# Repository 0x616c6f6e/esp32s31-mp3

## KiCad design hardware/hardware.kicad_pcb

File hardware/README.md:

# ESP32-S31 MP3 · 紧凑版硬件 Rev A

本目录为基于原始嘉立创工程迁移、修正并缩小的 KiCad 10 工程。PCB 为 **48 × 76 mm、六层、R1.2 mm 圆角**，比原版 50 × 80 mm 面积减少 **8.8%**。这是可继续编辑和结构评审的版本，尚未完成整机装配及实物电气验证。

## 打开与预览

使用 **KiCad 10.0.4 或兼容版本**打开 `hardware.kicad_pro`，从项目管理器进入原理图和 PCB。符号、封装均使用本目录相对路径，不依赖嘉立创在线库。

- `hardware.kicad_sch`：总览及九张子页。
- `hardware.kicad_pcb`：126 个封装，已布线、铺铜。
- `MP3_Source.kicad_sym`、`MP3_Source.pretty/`：工程内符号和 42 个封装文件。
- `output/layout-overview.png`：正反面布局和尺寸预览。
- `output/assembly-top.svg`、`assembly-bottom.svg`：实际封装装配图。
- `output/schematic/`：十张原理图 SVG。
- `output/board-only.step`：KiCad 导出的板体 STEP；FreeCAD 实体复核为 48 × 76 × 0.91 mm，导出板体未包含外表铜及阻焊的厚度。结构预留应按暂定名义板厚 1.0 mm 加公差计算；不含元件、屏幕、电池或外壳。
- `output/pcb-top.png`：KiCad 裸板渲染。原始工程没有可用的完整元件三维模型，不能用它判断器件高度。
- `output/drc.json`、`erc.json`、`netlist.xml`、`validation-summary.json`：检查报告及网络表。

## 本次修改

1. 从 `.epro2` 原工程导出兼容的 EasyEDA Pro V2 工程，再用 KiCad 原生导入，保留原器件封装和六层连接。原始 Gerber 作为原版层数和外形依据；新板没有直接复用 Gerber 图形充当可编辑布线。
2. 保留顶部 TF 卡座、右上主控、左下音频、右下充电供电、底部 USB-C / 耳机座、背面屏幕 FPC 的功能布局；压缩功能区间隙并收紧外框，重布受影响网络和局部地连接。
3. 修复跨页网络标签、短接符号和导入形成的微小断线；统一网络别名，记录在 `reference/net-aliases.json`。原理图网格整理和悬空线段清理前后，168 组“器件引脚集合”的连接分组保持一致。
4. 按 CS43131 数据手册修正 U2 的 I²C 引脚：**1 脚 SCL、39 脚 SDA**，并同步修正 PCB。补全 C32 / C33 晶振电容的原理图接地。修正可选下载电路的 BOOT 网络名。
5. 校正主要芯片引脚电气类型和电源驱动标识；保留原工程排除出 PCB 的可选电路，不将缺件强行补装。排除项包括 Q1、Q2、R23、R24、C13、R15、R16、U10、R6、C52、C60；具体以原理图的 `on_board` / DNP 属性为准。
6. 将原来落在 Edge.Cuts 上、不能约束铜层的天线禁布区修正为六层铜禁布，重新铺铜。板顶约 6.169 mm 范围禁止走线、过孔、铺铜；为保留 SCREW5 非金属化孔，区域允许焊盘对象，另外核对现有铜焊盘均未侵入此区域。以后移动或增加器件时必须重新核对。
7. 移除原版板框外的 SCREW3，将其余四个安装孔改为 Ø2.2 mm NPTH，供 M2 安装使用。源封装中的零环宽镀铜孔不再沿用。
8. 将不适合印刷的源封装轮廓转到 Fab 层，整理原理图页框、说明和目录，清除无效导入图形。装配时应参考 Fab 图；生产丝印仍应按最终装配需求补充。

## 尺寸和结构约束

[山灵 Q2 官方代理商发布资料](https://prtimes.jp/main/html/rd/p/000000232.000139013.html)给出的整机尺寸是 **80 × 50 × 13.5 mm**，屏幕突出部最大厚度 14.2 mm。本版以不超过其长宽为目标，但 **PCB 长宽合适不等于整机已经装得下**。

| 项目 | 当前值 / 状态 |
| --- | --- |
| 板框 | 宽 48.00 × 高 76.00 mm；圆角 R1.20 |
| 板厚 | 暂定 1.00 mm，需板厂确认六层叠层 |
| 耳机座 | 源封装边界伸出底边约 2.19 mm |
| USB-C | 源封装边界伸出底边约 1.22 mm |
| 板框加底部接口的纵向占用 | 约 78.19 mm，未计实物尺寸误差和外壳壁厚 |
| 屏幕 | 原工程标注 2.09 英寸、320 × 375、QSPI；缺完整屏体 / FPC 折弯结构模型 |
| 安装方式 | 4 个 M2 通孔；靠右的螺钉头及柱外径需要单独校核 |
| 外壳 | 当前外观方向为 [Q2 修订 C](../mechanical/enclosure-q2-c/README.md)，50 × 80 × 13.5 mm、含盖板 14.2 mm；现有 PCB 与大圆角壳体有干涉，须改板。旧 A 版仅保留追溯 |

以下孔中心以 PCB 左上角为原点，X 向右、Y 向下，单位 mm。KiCad 绝对原点为 `(100, 50)`。

| 孔位 | X | Y | 孔径 |
| --- | ---: | ---: | ---: |
| SCREW1 | 3.0615 | 69.9635 | 2.20 NPTH |
| SCREW2 | 11.5730 | 34.3608 | 2.20 NPTH |
| SCREW4 | 45.8365 | 34.7870 | 2.20 NPTH |
| SCREW5 | 10.8085 | 3.7485 | 2.20 NPTH |

上述接口伸出量由源封装图形估算，不代替连接器尺寸图。天线周围还必须避开金属外壳、屏幕金属背板和电池铝箔；建议顶部使用非金属射频窗口，并按[乐鑫硬件设计指南](https://documentation.espressif.com/esp-hardware-design-guidelines/en/latest/esp32s31/index.html)完成整机射频复核。

## 检查结果与范围

2026-09-21，使用 KiCad 10.0.4：

| 检查 | 结果 |
| --- | --- |
| PCB DRC，重新铺铜后 | 0 错误、0 警告 |
| 未连接项目 | 0 |
| 原理图 / PCB 一致性 | 0 差异 |
| ERC | 0 错误、9 警告 |
| 原理图网格及悬空线整理 | 168 组引脚连接分组一致 |
| 当前铜焊盘侵入天线区 | 0 |
| 裸板 STEP / FreeCAD 1.1.1 | 单一有效实体，48 × 76 × 0.91 mm 板体 |

ERC 的 9 条警告均为单引脚网络标签：`ESP_IO5`、`STC3115_ALM`、`BQ25895_USB_DP`、`BQ25895_USB_DN`、`BQ25895_STAT`、`BQ25895_QON#`、`BQ25895_DSEL`、`GEK100_KEY`、`GEK100_RST`。它们没有被隐藏或改成已接通；其中 KEY 的外接按钮必须处理，其他信号应按最终产品功能决定接出或不用。

报告中的 `ignored_checks` 明确列出了工程未启用的检查类别，例如缺少 courtyard、封装类型/过滤器检查、单次全局标签等；“0 DRC”仅指当前规则下的检查通过，不代表所有制造能力和电气性能均已验证。

## 打样前必须完成

- **开机按钮**：GEK100 的 KEY 必须通过外部常开按钮接 GND。本版本尚未新增按钮座或按钮器件，不能据此认定离线开机功能完整。KEY 内置上拉、RST 内置下拉；按[厂家数据手册](https://gsctek.com/uploads/allimg/20251225/1-251225110HM63.pdf)确认订货后缀。原图注释为 GEK100-57，采购和开关时序必须对应。
- **下载方式**：原版自动下载三极管为未装/不进 PCB 的可选部分；需要在样机确认原生 USB 下载、BOOT / EN 操作和恢复方式，不能假设 CH343 已实现自动下载。
- **板厂叠层与 USB**：六层板厚暂定 1.0 mm；最小线宽/间距 0.127 mm，新增过孔 0.50/0.25 mm。USB 差分的 90 Ω 目标仍需结合实际介质、铜厚、参考层计算和复核，尚未做阻抗或信号完整性仿真。
- **USB-C 内部槽**：`hardware.kicad_dru` 仅对 USB1 封装内部定位槽采用 0.15 mm 铜到槽边要求，源几何约 0.173 mm；外板边仍要求 0.30 mm。必须让板厂接受该局部工艺，或更换连接器封装重新布线。
- **器件/结构实物确认**：屏幕外形现已按用户图纸建模为 36.33 × 43.45 × 1.46 mm、显示区 34.18 × 40.05 mm；其连接器、引脚排列和折弯半径仍需核对。Q2 修订 C 已把 ESP32 面朝屏幕、FPC2 朝后盖，并新增独立滑环/按键小板的机械模型；仍检出旧板及 U9/H1/C5/C58/CN1 包络与壳体相交，屏幕上移也影响天线净空；旧 A 版的无干涉结果不能用于新外观。电池、插座实物高度和操作环电路仍待落实。
- **上电验证**：按限流供电逐项验证充电和电源轨、启动、屏幕/TF、DAC 的 I²C 和音频输出、噪声、射频及热表现。ERC 的电气类型校正和 PWR_FLAG 标识不代替实测。

## 来源和备份

根目录的三份用户源文件保持原样：`esp32s31-mp3-lceda-pro.epro2`、`esp32s31-mp3-SCH_Schematic.pdf`、`esp32s31-mp3-lceda-pro_gerber.zip`。

`reference/initial-kicad/` 保存修改前的 KiCad 工程；`reference/original-v2.epro` 保存兼容导出；`reference/native-original.zip` 保存原生导入后的基线，供追溯使用，不是最终工程。原版 Gerber 不能用于生产新尺寸 PCB。

主要参考数据手册已保存为 `reference/esp32-s31-wroom-3.pdf`、`cs43131.pdf`、`bq25895.pdf`。

重新检查可在本目录执行：

```powershell
kicad-cli sch erc --format json -o output/erc.json hardware.kicad_sch
kicad-cli sch export netlist --format kicadxml -o output/netlist.xml hardware.kicad_sch
kicad-cli pcb drc --refill-zones --save-board --schematic-parity --format json -o output/drc.json hardware.kicad_pcb
```

检查报告对应当前保存版本；后续修改后需重新生成。当前未发布新板生产 Gerber。

## 工具连接状态

KiCad MCP 在本次会话的连接测试中可用，但服务器配置为只读；实际工程编辑使用本机 KiCad API / CLI。FreeCAD MCP 前期测试可用，最终 STEP 复核时其 RPC 返回连接被拒绝，且 MCP 的独立进程入口未配置 `freecadcmd`。已改用本机 `D:/FreeCAD/1.1/bin/freecadcmd.exe` 完成 STEP 几何复核，报告见 `output/step-validation.json`。这不影响保存好的 KiCad 工程；若继续通过 FreeCAD MCP 交互，需要恢复 FreeCAD 的 RPC 服务。

后续外壳设计任务中，FreeCAD MCP 的 RPC 已恢复正常。最新内部装配修订 C 位于 `mechanical/enclosure-q2-c/`（操作小板仅机械外形，电路待实现）；B 版外观与独立 LCD 工程位于 `mechanical/enclosure-q2/`；旧 A 版位于 `mechanical/enclosure/`。本次外观修订未改写 KiCad 板文件，不应将原板 DRC 通过视作已经适配新壳。

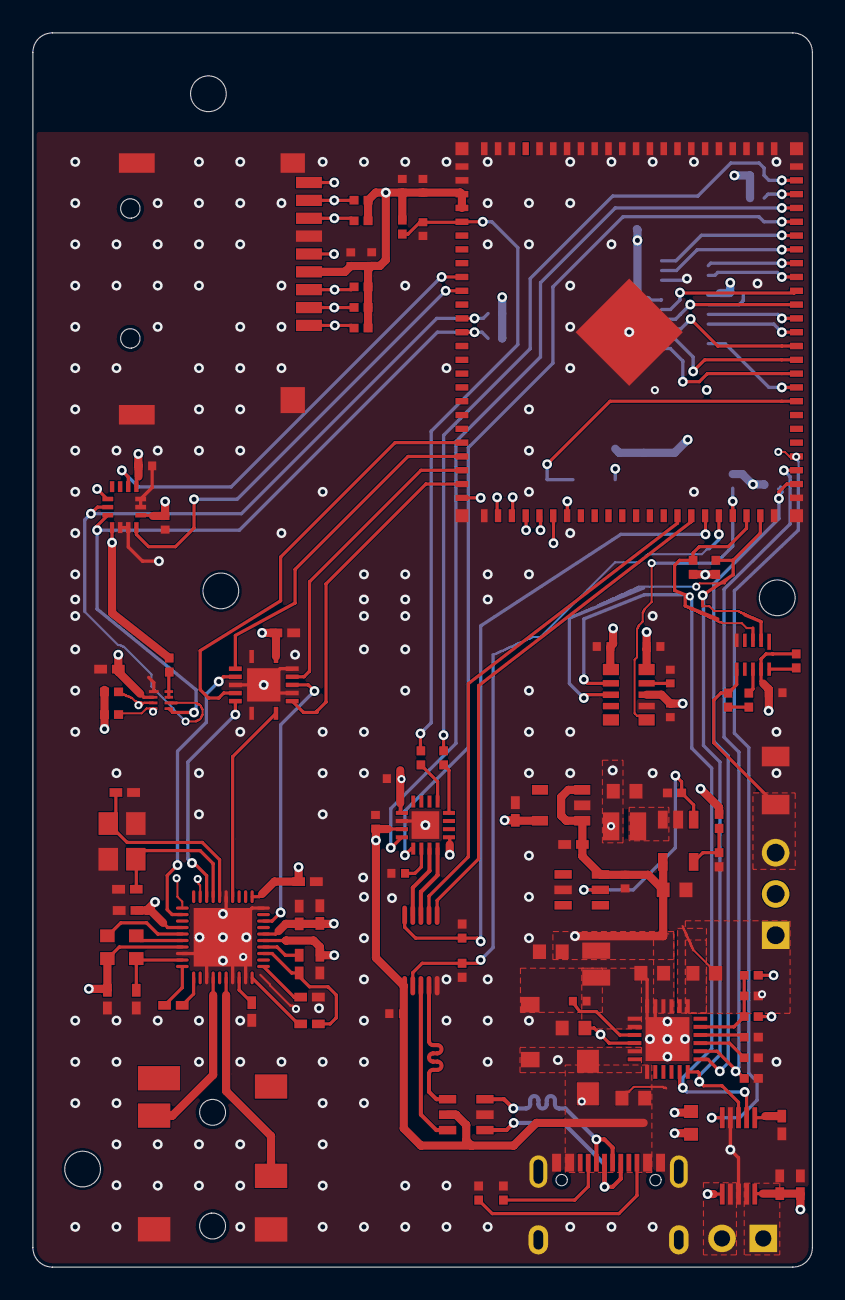
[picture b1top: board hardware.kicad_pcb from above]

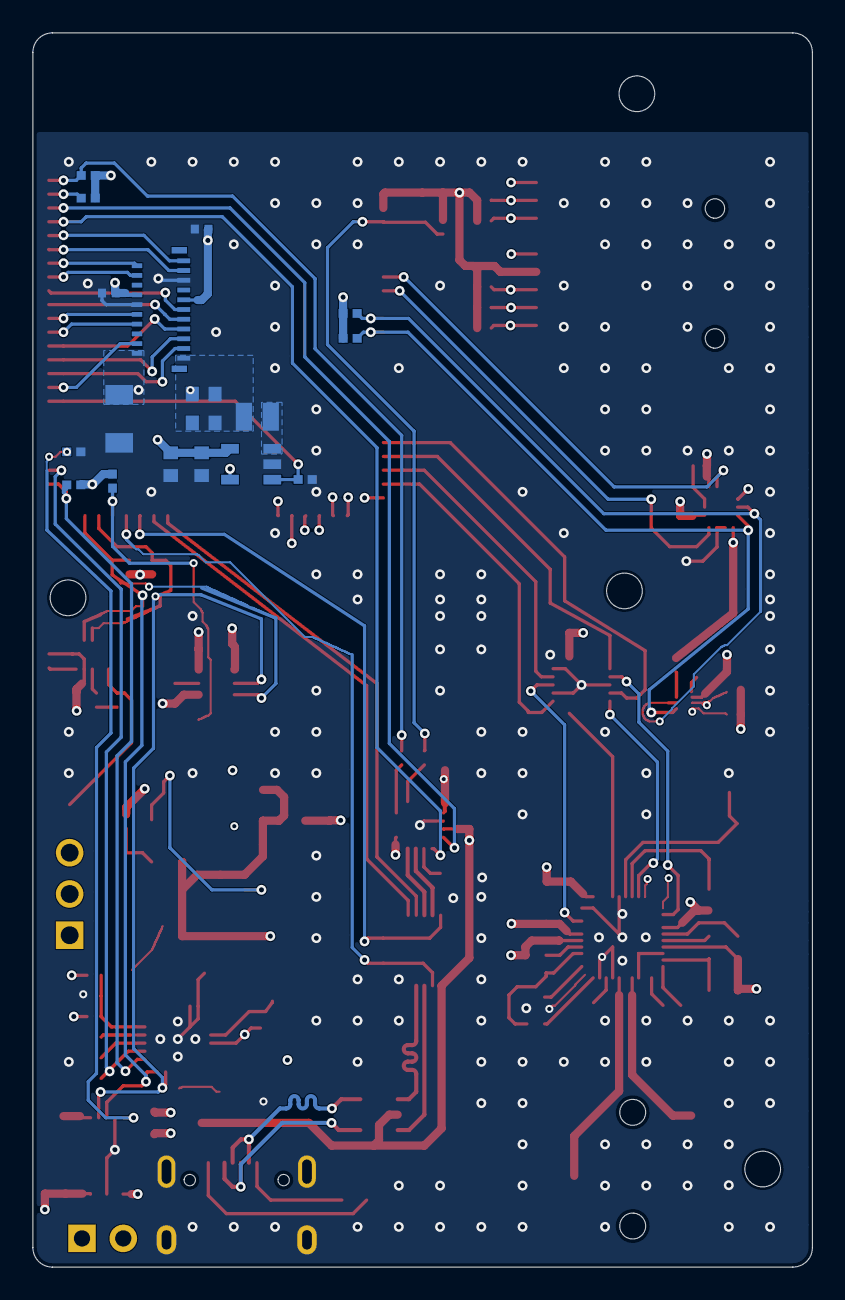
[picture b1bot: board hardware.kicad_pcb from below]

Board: 6 copper layers, 48.0 x 76.0 mm, 126 parts (18 on the bottom side), 104 nets.

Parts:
C1: 10uF; C0603_1_C1
C2: 10uF; C0603_1_C2
C3, C6, C7, C36, C37, C38, C40, C44, C45, C46, C47, C48, C50, C53: 100nF; C0402
C4, C5, C30, C31: 1uF; C0402_1
C8, C18: 22uF; C0603
C9: 4.7uF; C0603_1_C9
C10: 10uF; C0603_1_C10
C11: 47nF; C0402
C12: 10uF; C0603_1_C12
C14: 1uF; C0603_1_C14
C15: 10uF; C0603_1_C15
C16: 47uF; C0805
C17, C19, C20, C21, C22, C23, C24, C25: 2.2uF; C0402_1
C26: 4.7uF; C0402_1
C27, C28, C29, C34, C35, C58: 100nF; C0402_1
C32, C33: 10pF; C0402_1
C39, C41, C54: 1uF; C0402
C42, C55, C56, C57: 10uF; C0603_1
C43: 220nF; C0402
C49: 10uF; C0402
CARD2: TF PUSH; TF-SMD_TF-PUSH
CN1: PJ-342B-TX-SMT; AUDIO-SMD_PJ-342B-TX-SMT
D1: USBLC6-2SC6; SOT-23-6_L2.9-W1.6-P0.95-LS2.8-BL
D2: B5817W; SOD-123_L2.8-W1.8-LS3.7-RD
FPC2: 2.09寸320*375高清R角方屏QSPI; CONN-TH-21P_AFE03-S21FMA-1H
H1: HDR-TH_2P-P2.54-V-F
H2: HDR-TH_3P-P2.54-V-M
L1, L2: 2.2uH; IND-SMD_L2.0-W1.6
L3: BLM18KG601SN1D; L0603
L4: 4.7uH; IND-SMD_L2.0-W1.6
R1: 10mΩ; R1206
R2, R33: 1K; R0402
R3: 22K1; R0402
R4, R5, R11, R12, R21, R22, R41: 100K; R0402
R7, R8, R20, R25, R26, R29, R30, R35, R36, R37, R38, R39, R42, R43, R44: 10K; R0402
R9: 700R; R0402
R10, R34: 0R/NC; R0402
R13: 5K23; R0402
R14: 30K1; R0402
R17: 200K; R0402_2
R18, R19: 10K; R0402_1
R27, R28: 0/NC; R0402
R31, R32: 5K1; R0402
R40: 1R5; R1206
SCREW1, SCREW2, SCREW4, SCREW5: M2 clearance 2.2mm; MountingHole_2.2mm
U1: RX8130CE:BB; RTC-SMD_L3.2-W2.5-P0.7-RX8130CE
U2: CS43131-CNZ; QFN-40_L5.0-W5.0-P0.40-TL-EP3.6_1
U3: DSCB_BQ25895RTW; WQFN-24_L4.0-W4.0-P0.50-TL-EP2.7
U4: TLV62568DBVR; SOT-23-5_L3.0-W1.7-P0.95-LS2.8-BR
U5: ME6211C18M5G-N; SOT-23-5_L3.0-W1.7-P0.95-LS2.8-BR_1
U6: GEK100; SOT-23-6_L2.9-W1.6-P0.95-LS2.8-BL-2
U7: PCA9306DQER; X2SON-8_L1.4-W1.0-P0.35-BL
U8: SN74LV4T125RGYR; VQFN-14_L3.5-W3.5-P0.50-BL-EP
U9: ESP32-S31-WROOM-3-N16R16V; CONN-SMD_ESP32-S31-WROOM-3
U11: DRV2605LDGSR; VSSOP-10_L3.0-W3.0-P0.50-LS4.9-BL
U12: CH343P; TQFN-16_L3.0-W3.0-P0.50-BL-EP1.7
U14: STC3115AIQT; DFN-10_L3.0-W2.0-P0.50-BL
U15: LSM6DS3TR-C; LGA-14_L3.0-W2.5-P0.50-TL
U16: PAM2804AAB010; SOT-23-5_L3.0-W1.7-P0.95-LS2.8-BR
U17: SGM7229YMS10G/TR; MSOP-10_L3.0-W3.0-P0.50-LS4.9-BL
USB1: TYPE-C 16PIN 2MD(073); USB-C-SMD_TYPE-C-16PIN-2MD-073
X1: 26MHz; CRYSTAL-SMD_4P-L3.2-W2.5-BL_1

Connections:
BAT_TS: H2.2, R10.1
BQ25895_CHG_EN#: R11.2, U3.9
BQ25895_I2C_CLK: R7.2, U1.2, U3.5, U9.45, U11.2, U14.3
BQ25895_I2C_SDA: R8.2, U1.3, U3.6, U9.46, U11.3, U14.2
BQ25895_INT: R43.2, U3.7, U9.49
BQ25895_OTG_EN: R12.2, U3.8, U9.50
CH343P_UART_DTR: R28.2, U12.12
CH343P_UART_RTS: R27.1, U12.13
CH343P_UART_RX: U9.68, U12.5
CH343P_UART_TX: U9.69, U12.4
CH343P_USB_DN: U12.8, U17.8
CH343P_USB_DP: U12.7, U17.9
CS43131_I2S_LRCK: U2.38, U8.6
CS43131_I2S_SCLK: U2.34, U8.8
CS43131_I2S_SDIN: U2.2, U8.3
CS43131_RST#_1V8: U2.28, U8.11
CS43131_SCL_1V8: R18.1, U2.1, U7.3
CS43131_SDA_1V8: R19.1, U2.39, U7.4
DAC_I2C_SCL: R26.2, U7.6, U9.12, U15.13
DAC_I2C_SDA: R30.2, U7.5, U9.13, U15.14
DAC_I2S_LRCK: U8.5, U9.21
DAC_I2S_SCLK: U8.9, U9.24
DAC_I2S_SDIN: U8.2, U9.22
DAC_RST#: U8.12, U9.23
ESP32S31_EN: C39.1, R27.2, R29.1, U9.5
ESP_BOOT1: R20.2, R28.1, U9.71
ESP_BOOT2: R25.2, U9.70
ESP_I2C2_SCL: FPC2.19, U9.66
ESP_I2C2_SDA: FPC2.20, U9.65
ESP_IO1: U9.9, U15.9
ESP_IO4: U9.10, U15.4
ESP_IO19: CARD2.CD, U9.25
ESP_IO33: R21.2, U9.42, U17.10
ESP_IO34: R22.1, U9.43, U17.2
ESP_IO35: R42.1, U1.6, U9.44
ESP_IO40: R44.2, U9.51, U11.5
ESP_IO45: R41.2, U9.55, U16.1
ESP_IO46: FPC2.4, U9.56
ESP_IO47: FPC2.3, U9.57
ESP_IO54: FPC2.18, U9.64
ESP_IO57: FPC2.21, U9.67
ESP_SPI2_CLK: FPC2.5, U9.58
ESP_SPI2_CS: FPC2.7, U9.59
ESP_SPI2_D0: FPC2.11, U9.63
ESP_SPI2_D1: FPC2.10, U9.61
ESP_SPI2_D2: FPC2.9, U9.62
ESP_SPI2_D3: FPC2.8, U9.60
ESP_TF_CLK: CARD2.5, U9.31
ESP_TF_CMD: CARD2.3, R39.2, U9.32
ESP_TF_DAT0: CARD2.7, R38.2, U9.27
ESP_TF_DAT1: CARD2.8, R35.2, U9.28
ESP_TF_DAT2: CARD2.1, R36.2, U9.29
ESP_TF_DAT3: CARD2.2, R37.2, U9.30
ESP_USB_DN: U9.41, U17.6
ESP_USB_DP: U9.40, U17.7
GBAT: H2.3, R1.1, R34.1, U14.6
GND: C1.1, C2.1, C3.1, C4.1, C5.1, C6.2, C7.2, C9.2, C10.1, C12.1, C14.1, C15.1, C16.2, C17.2, C19.2, C21.2, C22.2, C23.1, C26.2, C27.2, C28.2, C29.2, C30.1, C31.1, C32.1, C33.2, C34.2, C35.1, C36.2, C37.2, C38.2, C39.2, C40.2, C41.2, C42.1, C43.2, C44.2, C45.2, C46.2, C47.2, C48.2, C49.1, C50.1, C53.2, C54.2, C55.1, C56.1, C57.1, C58.1, CARD2.6, CARD2.10, CARD2.11, CARD2.12, CARD2.13, CN1.2, CN1.5, D1.2, FPC2.12, FPC2.17, R1.2, R3.1, R5.1, R9.1, R11.1, R12.1, R14.1, R21.1, R22.2, R31.1, R32.1, R40.1, R41.1, R44.1, U1.7, U2.8, U2.13, U2.17, U2.19, U2.30, U2.35, U2.41, U3.17, U3.18, U3.25, U4.2, U5.2, U6.2, U7.1, U8.1, U8.4, U8.7, U8.10, U8.13, U8.15, U9.1, U9.2, U9.26, U9.47, U9.48, U9.72, U9.73, U9.74, U9.75, U9.76, U9.77, U9.78, U9.79, U9.80, U9.81, U9.82, U9.83, U9.84, U9.85, U9.86, U9.87, U9.88, U9.89, U9.90, U9.92, U9.93, U9.94, U9.95, U9.96, U9.97, U9.98, U9.99, U11.4, U11.8, U12.2, U12.17, U14.5, U15.2, U15.3, U15.6, U15.7, U16.2, U17.5, USB1.13, USB1.14, USB1.A1B12, USB1.B1A12, X1.2, X1.4
LCD_LEDA: C42.2, C55.2, FPC2.1, L4.2
LCD_LEDK: FPC2.2, R40.2, U16.5
MOTOR_OUT_N: H1.1, U11.9
MOTOR_OUT_P: H1.2, U11.7
unnamed: C11.2, D2.2, L2.1, U3.19, U3.20
unnamed: R33.2, R34.2
unnamed: C54.1, U1.9
unnamed: C8.1, U2.5
unnamed: C18.1, U2.6
unnamed: C24.2, C25.2, U2.23
unnamed: C20.2, U2.11
unnamed: C25.1, U2.20
unnamed: C20.1, U2.10
unnamed: C24.1, U2.24
unnamed: CN1.3, U2.14
unnamed: CN1.6, U2.16
unnamed: C21.1, U2.21
unnamed: C22.1, U2.18
unnamed: C33.1, U2.37, X1.3
unnamed: C32.2, U2.36, X1.1
unnamed: C18.2, C19.1, U2.9
unnamed: C11.1, U3.21
unnamed: R9.2, U3.10
unnamed: C9.1, R13.1, U3.22
unnamed: R10.2, R13.2, R14.2, U3.11
unnamed: R3.2, R4.1, U4.5
unnamed: L1.1, U4.3
unnamed: R17.1, U7.7, U7.8
unnamed: C4.2, U11.1
unnamed: C5.2, C58.2, L3.1, U11.6, U11.10
unnamed: C38.1, U12.6
unnamed: R33.1, U14.8
unnamed: R2.1, U14.10
unnamed: L4.1, U16.3
unnamed: R31.2, USB1.A5
unnamed: R32.2, USB1.B5
PWR_3V3_EN: R5.2, U4.1, U6.5
TYPEC_USB_DN: D1.4, U17.4
TYPEC_USB_DN_IN: D1.3, USB1.A7, USB1.B7
TYPEC_USB_DP: D1.6, U17.3
TYPEC_USB_DP_IN: D1.1, USB1.A6, USB1.B6
VBAT: C7.1, C10.2, C43.1, H2.1, R2.2, U1.10, U3.13, U3.14, U14.9
VBUS_5V: C14.2, C36.1, C44.1, D1.5, U3.1, U12.3, U12.9, U17.1, USB1.A4B9, USB1.B4A9
VCC: C1.2, C3.2, C12.2, C15.2, C26.1, C29.1, C30.2, L2.2, U2.26, U3.15, U3.16, U4.4, U5.1, U5.3, U6.6
VCC_1V8: C8.2, C17.1, C23.2, C27.1, C28.1, C31.2, C34.1, C35.2, R18.2, R19.2, U2.4, U2.7, U2.25, U2.31, U5.5, U7.2, U8.14
VCC_3V3: C2.2, C6.1, C37.1, C40.1, C41.1, C45.1, C46.1, C47.1, C48.1, C49.2, C50.2, C53.1, CARD2.4, FPC2.13, FPC2.14, L1.2, R4.2, R7.1, R8.1, R17.2, R20.1, R25.1, R26.1, R29.2, R30.1, R35.1, R36.1, R37.1, R38.1, R39.1, R42.2, R43.1, U1.1, U1.8, U9.3, U9.4, U12.1, U15.1, U15.5, U15.8, U15.12
VCC_LCD_BG: C16.1, C56.2, C57.2, D2.1, L3.2, U3.23, U16.4
